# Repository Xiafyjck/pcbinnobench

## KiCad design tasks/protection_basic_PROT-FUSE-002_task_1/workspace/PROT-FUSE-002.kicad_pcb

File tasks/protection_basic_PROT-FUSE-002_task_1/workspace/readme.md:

# PROT-FUSE-002

Use unidirectional TVS diode for surge protection.

In industrial applications, 12V may be slightly higher; this design tentatively uses 15V rating.

Includes fuse design.

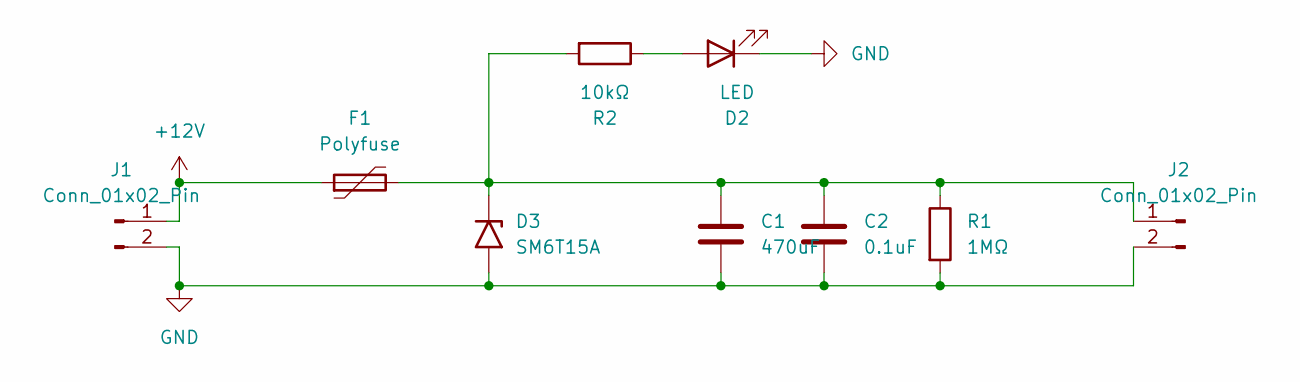
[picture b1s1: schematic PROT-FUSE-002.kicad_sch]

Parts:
C1: 470uF; C_Disc_D9.0mm_W5.0mm_P10.00mm
C2: 0.1uF; C_0805_2012Metric
D2: LED; LED_0805_2012Metric
D3: SM6T15A; D_SMB
F1: Polyfuse; L_0201_0603Metric
J1: Conn_01x02_Pin; JST_NV_B02P-NV_1x02_P5.00mm_Vertical
J2: Conn_01x02_Pin; JST_EH_B2B-EH-A_1x02_P2.50mm_Vertical
R1: 1MΩ; R_0805_2012Metric
R2: 10kΩ; R_0805_2012Metric

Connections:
+12V: F1.1, J1.1
GND: C1.2, C2.2, D2.1 (K), D3.2 (A2), J1.2, J2.2, R1.2
unnamed: D2.2 (A), R2.1
unnamed: C1.1, C2.1, D3.1 (A1), F1.2, J2.1, R1.1, R2.2

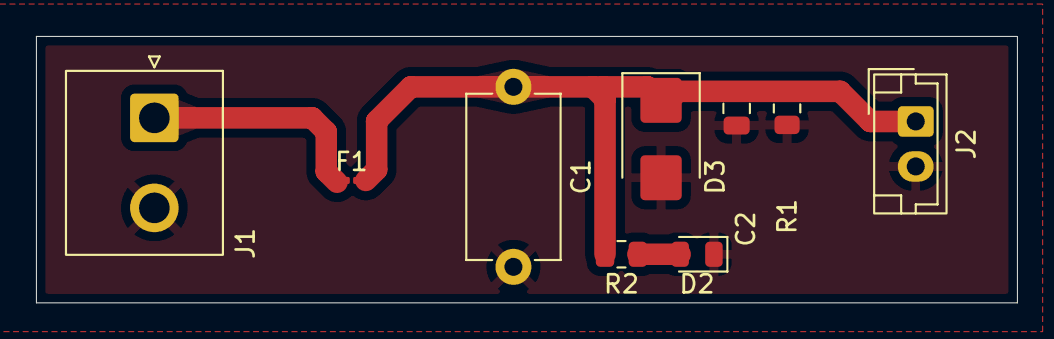
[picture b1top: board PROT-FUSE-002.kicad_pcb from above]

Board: 2 copper layers, 54.5 x 14.8 mm, 9 parts (0 on the bottom side), 4 nets.

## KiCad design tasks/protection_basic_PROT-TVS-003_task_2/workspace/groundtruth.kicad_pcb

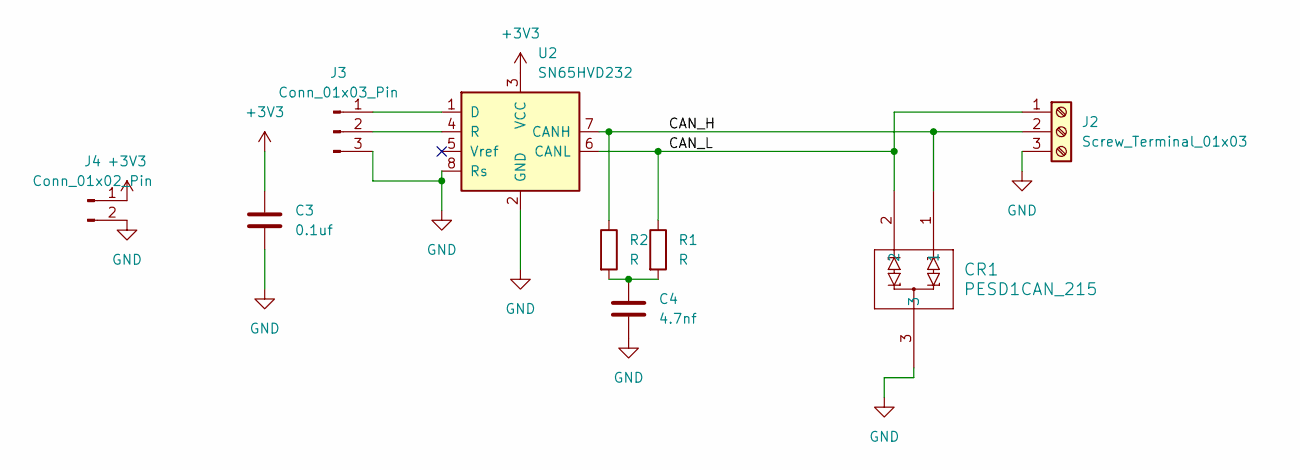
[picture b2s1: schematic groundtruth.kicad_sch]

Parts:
C3: 0.1uf; C_0805_2012Metric
C4: 4.7nf; C_0805_2012Metric
CR1: PESD1CAN_215; SOT23_PESD1_NEX
J2: Screw_Terminal_01x03; TerminalBlock_MaiXu_MX126-5.0-03P_1x03_P5.00mm
J3: Conn_01x03_Pin; PinHeader_1x03_P2.54mm_Vertical
J4: Conn_01x02_Pin; PinHeader_1x02_P2.54mm_Vertical
R1, R2: R; R_0805_2012Metric_Pad1.20x1.40mm_HandSolder
U2: SN65HVD232; SOIC-8_3.9x4.9mm_P1.27mm

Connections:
+3V3: C3.1, J4.1, U2.3 (VCC)
/CAN_H: CR1.1, J2.2, R2.1, U2.7 (CANH)
/CAN_L: CR1.2, J2.1, R1.1, U2.6 (CANL)
GND: C3.2, C4.2, CR1.3, J2.3, J3.3, J4.2, U2.2 (GND), U2.8 (Rs)
unnamed: C4.1, R1.2, R2.2
unnamed: J3.1, U2.1 (D)
unnamed: J3.2, U2.4 (R)

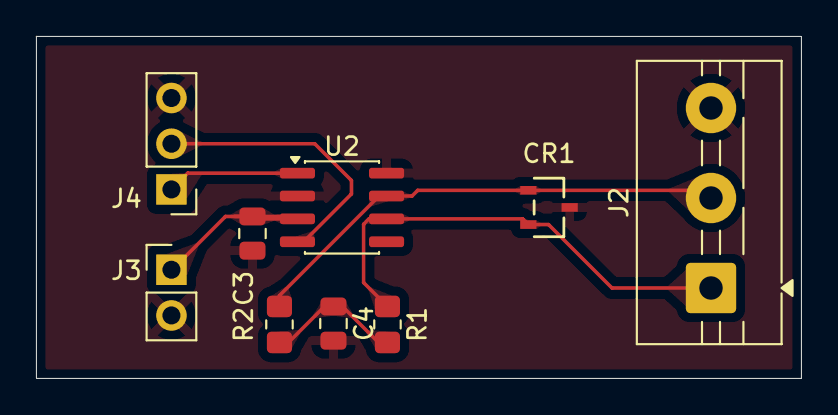
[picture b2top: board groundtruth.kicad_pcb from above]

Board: 2 copper layers, 42.5 x 19.0 mm, 9 parts (0 on the bottom side), 7 nets.

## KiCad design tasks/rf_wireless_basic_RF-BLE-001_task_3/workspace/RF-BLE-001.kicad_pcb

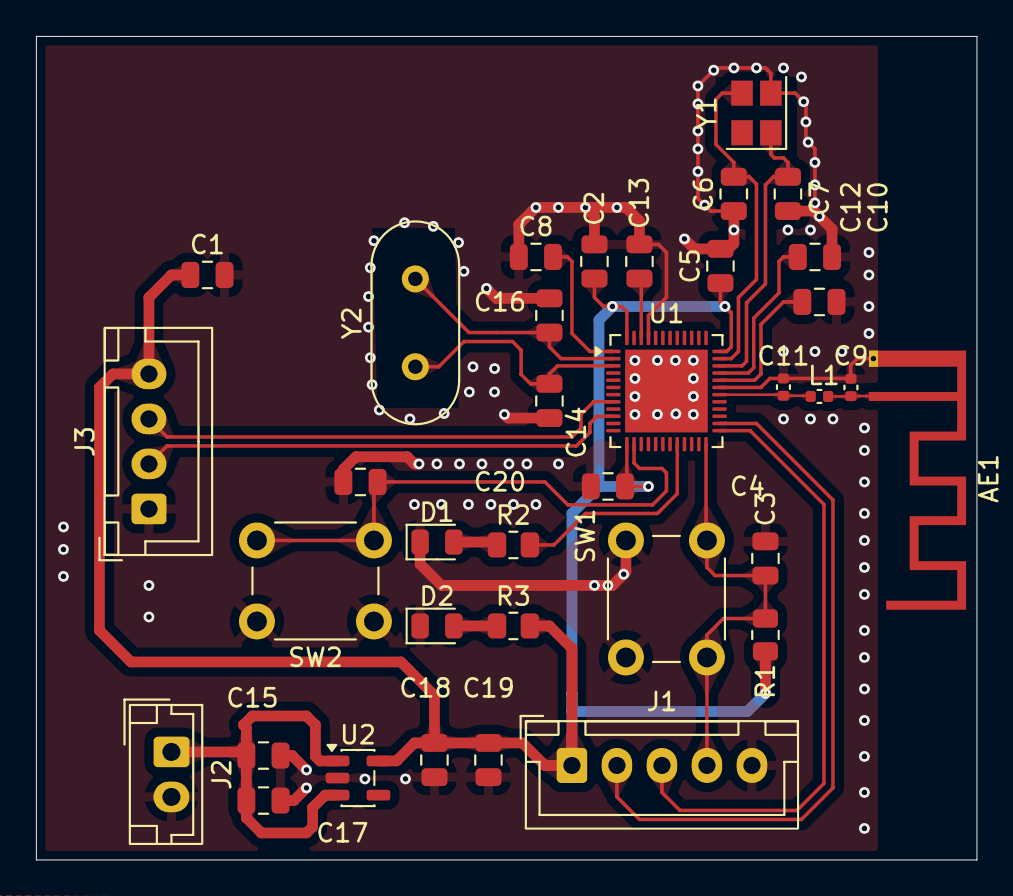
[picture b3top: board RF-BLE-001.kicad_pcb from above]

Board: 2 copper layers, 52.2 x 45.8 mm, 36 parts (0 on the bottom side), 22 nets.

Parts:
AE1: Antenna_Shield; Texas_SWRA117D_2.4GHz_Right
C1: 4.7uF; C_0805_2012Metric
C2, C3, C4, C5, C8, C12, C17, C18, C20: 100nF; C_0805_2012Metric
C6, C7: 8pF; C_0805_2012Metric
C9: NC; C_0402_1005Metric
C10: 100pF; C_0805_2012Metric
C11: 0.8pF; C_0402_1005Metric
C13: 1uF; C_0805_2012Metric
C14, C16: 12pF; C_0805_2012Metric
C15, C19: 10uF; C_0805_2012Metric
D1, D2: LED; LED_0805_2012Metric
J1: Conn_01x05_Pin; JST_XH_B5B-XH-A_1x05_P2.50mm_Vertical
J2: Conn_01x02_Pin; JST_EH_B2B-EH-A_1x02_P2.50mm_Vertical
J3: Conn_01x04_Pin; JST_XH_B4B-XH-A_1x04_P2.50mm_Vertical
L1: 3.9nH; C_0402_1005Metric
R1, R2, R3: 10kΩ; R_0805_2012Metric
SW1, SW2: SW_Push; SW_PUSH_6mm
U1: nRF52832-QFxx; QFN-48-1EP_6x6mm_P0.4mm_EP4.6x4.6mm
U2: TLV75533PDBV; SOT-23-5
Y1: 32MHz; Crystal_SMD_Abracon_ABM8AIG-4Pin_3.2x2.5mm
Y2: Crystal; Crystal_HC49-4H_Vertical

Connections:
+3.3V: C1.1, C2.1, C4.1, C5.1, C18.1, C19.1, J1.1, J3.4, R1.1, R3.2, U1.13 (VDD), U1.36 (VDD), U1.48 (VDD), U2.5 (OUT)
+5V: C15.1, C17.1, J2.1, U2.1 (IN), U2.3 (EN)
/NRST: C3.1, J1.4, R1.2, SW1.2, U1.24 (P0.21/~RESET)
/RX: J3.2, U1.10 (P0.08)
/TX: J3.3, U1.8 (P0.06)
/state_gpio: R2.2, U1.20 (P0.17)
/swclk: J1.3, U1.25 (SWDCLK)
/swdio: J1.2, U1.26 (SWDIO)
GND: AE1.2 (Shield), C1.2, C2.2, C3.2, C4.2, C5.2, C6.1, C7.1, C8.1, C9.1, C10.1, C11.1, C12.1, C13.1, C14.1, C15.2, C16.1, C17.2, C18.2, C19.2, C20.2, D1.1 (K), D2.1 (K), J1.5, J2.2, J3.1, SW1.1, SW2.1, U1.31 (VSS), U1.45 (VSS), U1.49 (VSS), U2.2 (GND), Y1.2
unnamed: AE1.1 (A), C9.2, L1.2
unnamed: D1.2 (A), R2.1
unnamed: D2.2 (A), R3.1
unnamed: C11.2, L1.1, U1.30 (ANT)
unnamed: C8.2, U1.1 (DEC1)
unnamed: C10.2, U1.32 (DEC2)
unnamed: C12.2, U1.33 (DEC3)
unnamed: C13.2, U1.46 (DEC4)
unnamed: C16.2, U1.2 (P0.00/XL1), Y2.2
unnamed: C14.2, U1.3 (P0.01/XL2), Y2.1
unnamed: C20.1, SW2.2, U1.14 (P0.11)
unnamed: C7.2, U1.34 (XC1), Y1.1
unnamed: C6.2, U1.35 (XC2), Y1.3
